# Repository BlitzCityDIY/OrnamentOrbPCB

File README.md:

# OrnamentOrbPCB
A simple PCB designed to resemble a classic orb ornament with spots for nine 5mm LEDs.

<b>*This design has just been sent off to fab and has not been recieved back yet, so the design has not been 100% tested.* </b>

But with the holidays coming I thought it might be fun to share the project just in case anyone wanted to view, modify or take a chance in sending their own off to fab in time for the impending 2018 holidays.

I'm including the Eagle files, BOM, .png art files and bitmap art files.

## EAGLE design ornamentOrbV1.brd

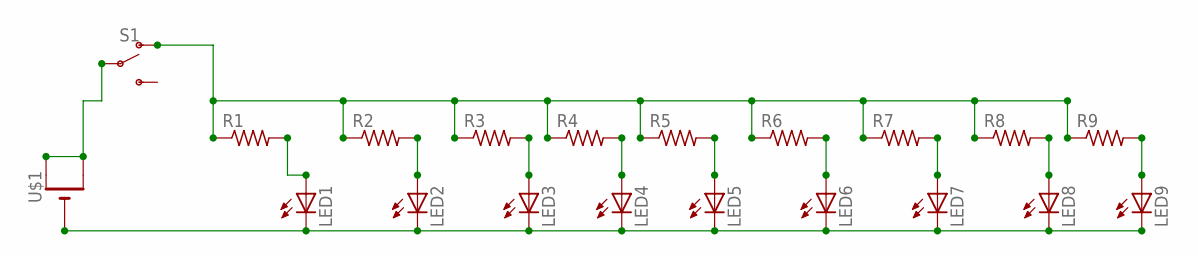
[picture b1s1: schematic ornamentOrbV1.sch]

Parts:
LED1, LED2, LED3, LED4, LED5, LED6, LED7, LED8, LED9: LED5MM
R1, R2, R3, R4, R5, R6, R7, R8, R9: R-US_R0805; R0805
S1: SWITCH-SPDT-SMD-RIGHT-ANGLE; SWITCH_SPST_SMD_A
U$1: CR2032SMT; CR2032-SMD

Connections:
unnamed: LED1.A, R1.2
unnamed: LED2.A, R2.2
unnamed: LED3.A, R3.2
unnamed: LED4.A, R4.2
unnamed: LED5.A, R5.2
unnamed: LED6.A, R6.2
unnamed: LED7.A, R7.2
unnamed: LED8.A, R8.2
unnamed: LED9.A, R9.2
unnamed: LED1.K (C), LED2.K (C), LED3.K (C), LED4.K (C), LED5.K (C), LED6.K (C), LED7.K (C), LED8.K (C), LED9.K (C), U$1.-
unnamed: R1.1, R2.1, R3.1, R4.1, R5.1, R6.1, R7.1, R8.1, R9.1, S1.1 (O)
unnamed: S1.2, U$1.+$1 (+), U$1.+$2 (+1)

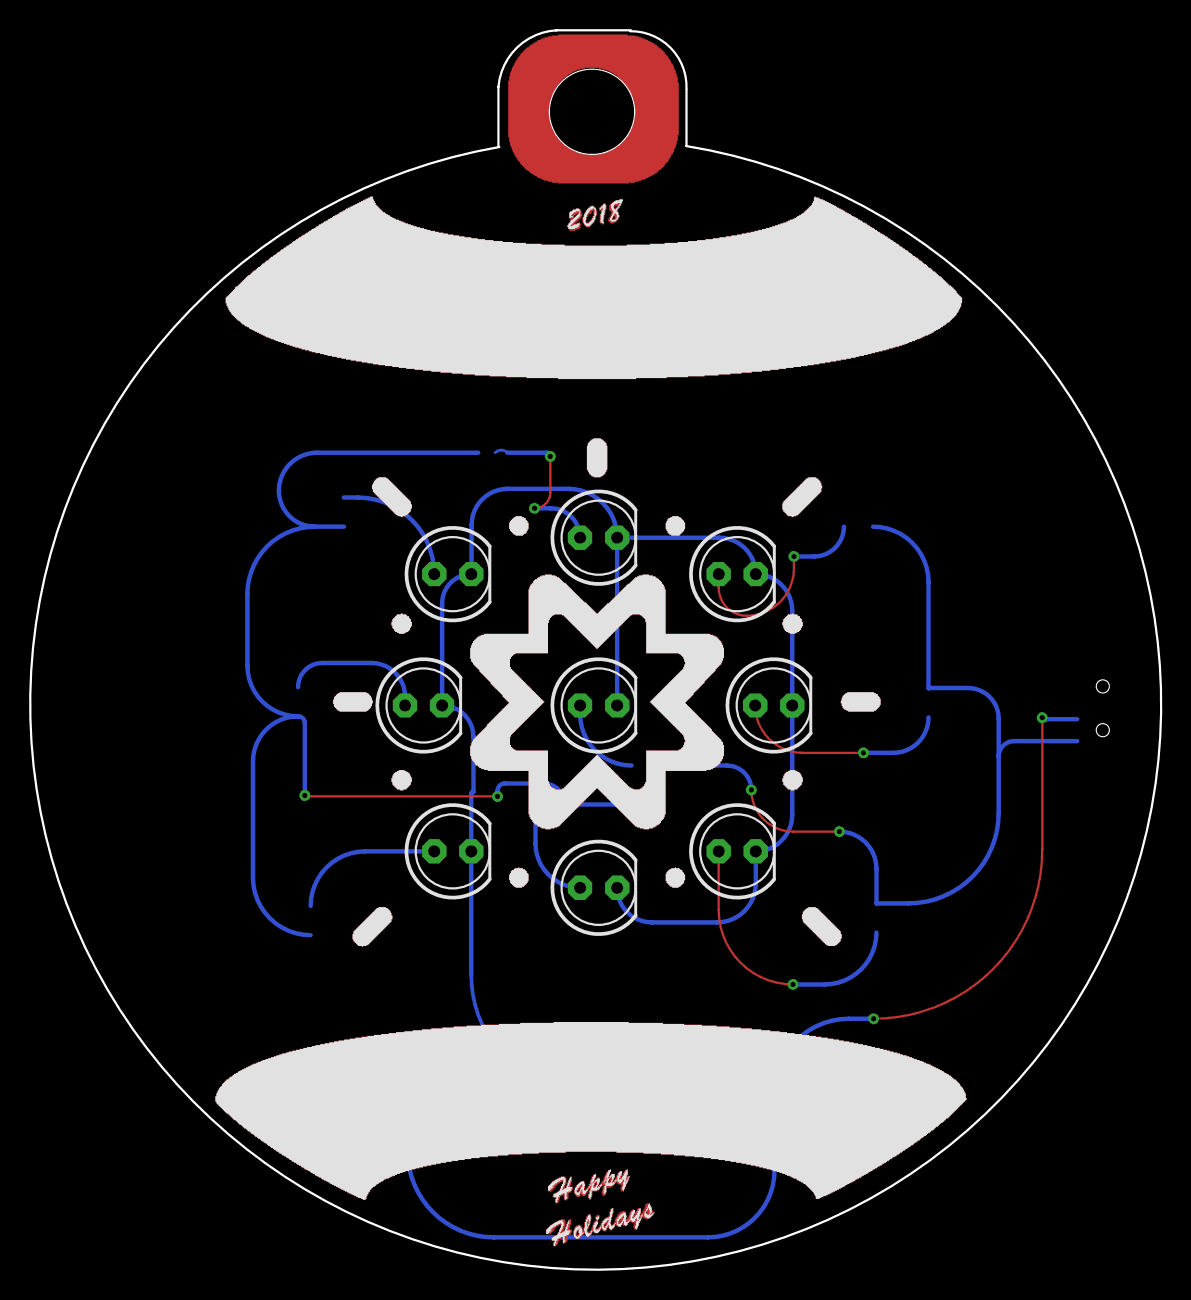
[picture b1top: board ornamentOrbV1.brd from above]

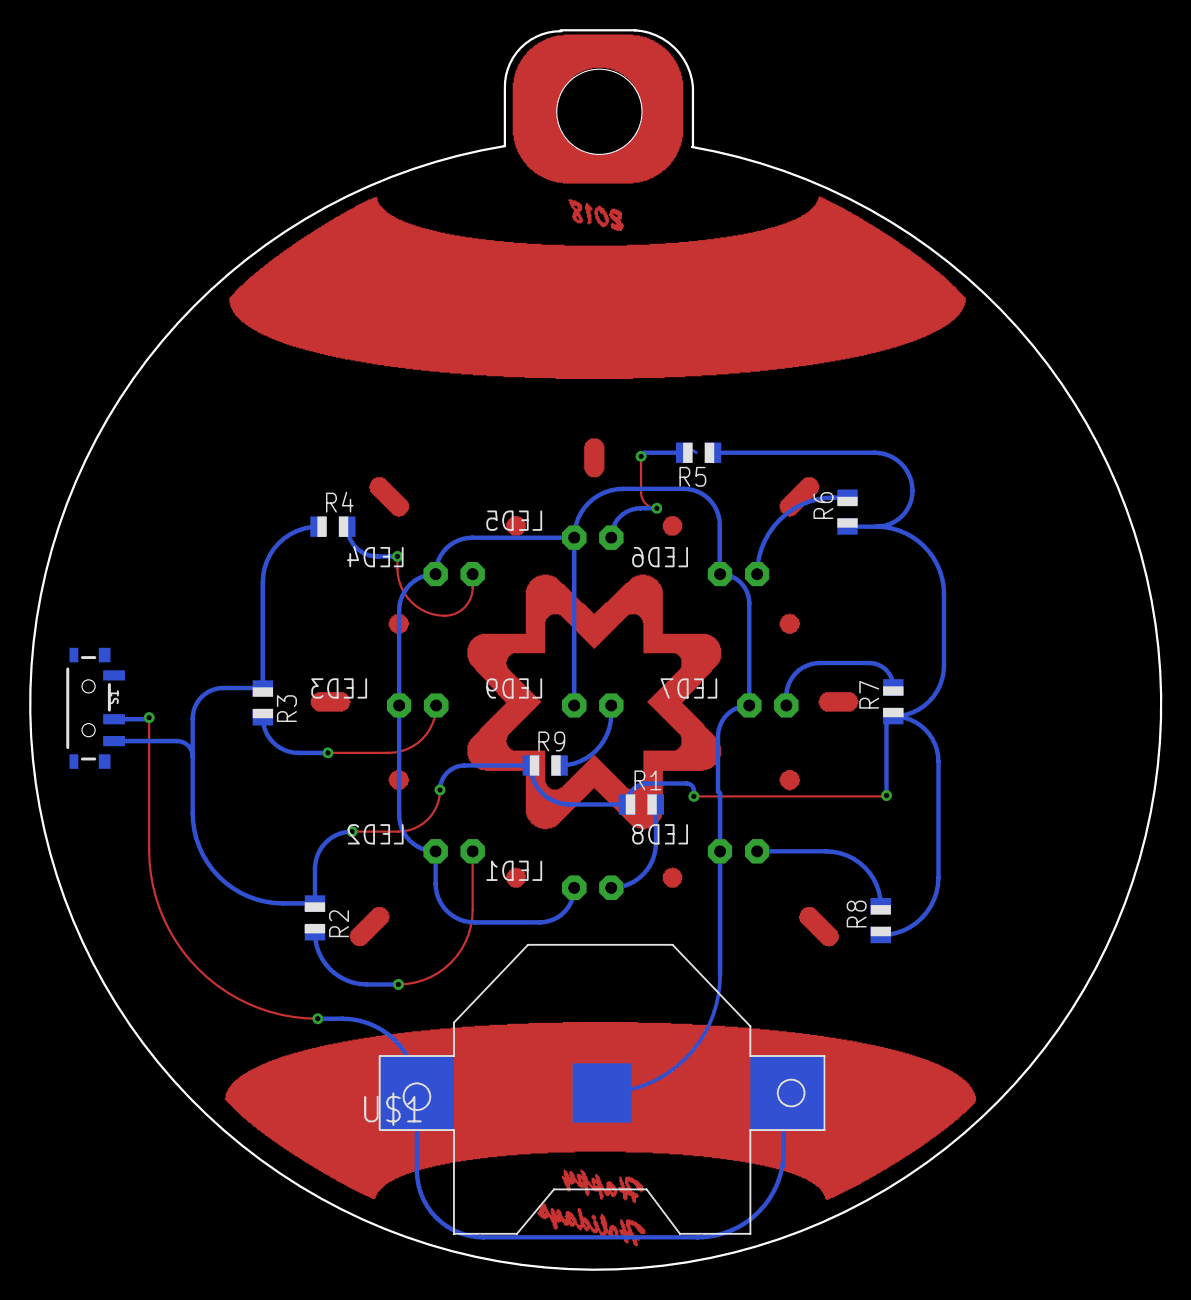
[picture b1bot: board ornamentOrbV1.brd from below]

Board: 2 copper layers, 77.5 x 85.0 mm, 20 parts (11 on the bottom side), 12 nets.

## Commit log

2018-11-29 Create OrnamentOrbV1_EagleBoardLayout
2018-11-29 .png art files
2018-11-29 bitmap art files
    400 ppi
2018-11-29 screenshot of board layout in Eagle
2018-11-29 adding image
2018-12-18 Updated .brd file
    Fixes missing trace for LED4

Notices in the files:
parts and their libraries:
SparkFun-Switches: Licensing: Creative Commons ShareAlike 4.0 International - https://creativecommons.org/licenses/by-sa/4.0
